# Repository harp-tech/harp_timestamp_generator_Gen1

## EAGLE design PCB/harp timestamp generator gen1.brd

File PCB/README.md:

# Harp Timestamp Generator Gen1

## Licensing

The designs, documentation, and photos available in this repository are free: you can redistribute it and/or modify it under the terms of the used license.
Check file named LICENSE.

Copyright Filipe Carvalho 2021

<br />This work is licensed under a <a rel="license" href="http://creativecommons.org/licenses/by-nc-sa/3.0/igo/">Creative Commons Attribution-NonCommercial-ShareAlike 3.0 IGO License</a>.

If your are interested in obtaining a license to sell this device, please contact filipe@open-ephys.org

[1]: https://docs.google.com/spreadsheets/d/1aobmmEzBDethzIlrm1eg0eYkBqlyX3s9WbA9KgRwVQI/edit?usp=sharing

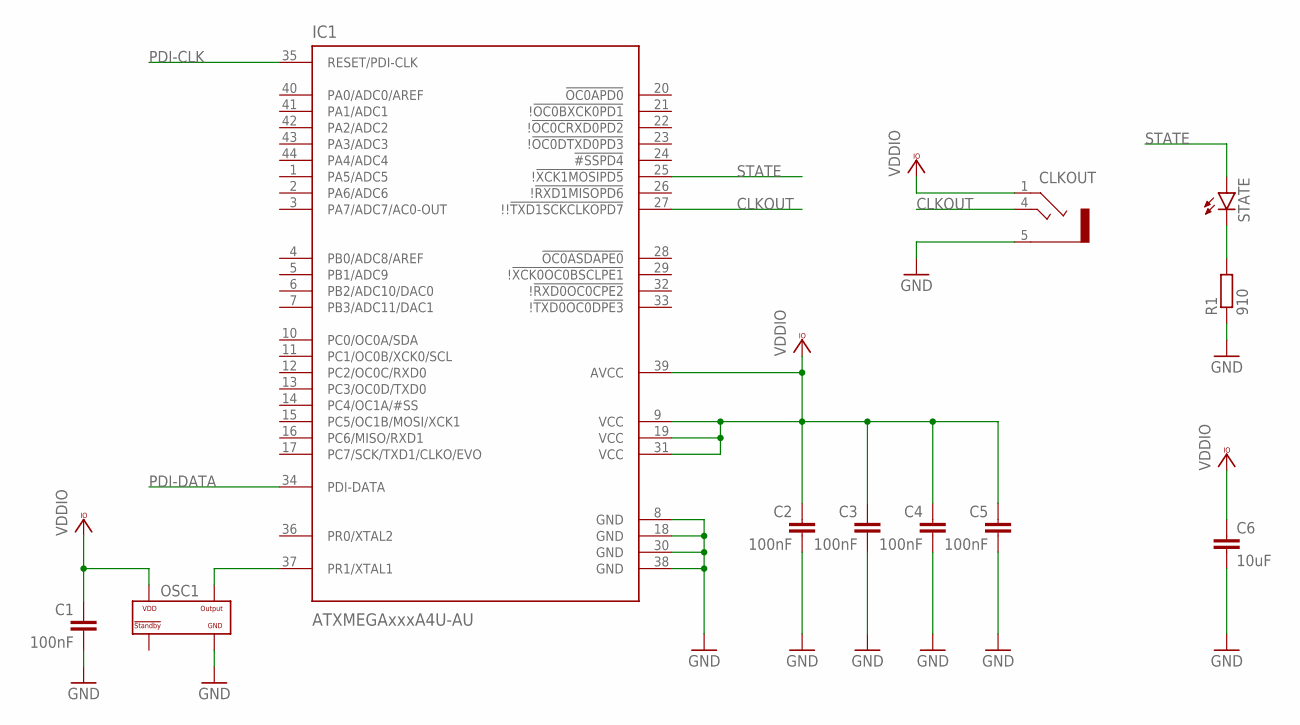
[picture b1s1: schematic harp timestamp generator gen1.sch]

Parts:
C1, C2, C3, C4, C5: 100nF; C0402
C6: 10uF; C0603
CLKOUT: STEREO_JACK; 35RASMT2BHNTRX
IC1: ATXMEGAxxxA4U-AU; QFP80P1200X1200X120-44N
OSC1: CNP-MISCELLANEOUS_OSCILLATOR; CNP-MISCELLANEOUS_OSCILLATOR_3.2X2.5
R1: 910; R0402
STATE: LEDCHIP-LED0603; CHIP-LED0603

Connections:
CLKOUT: CLKOUT.4, IC1.27 (!!!TXD1SCKCLKOPD7)
GND: C1.2, C2.2, C3.2, C4.2, C5.2, C6.2, CLKOUT.5, IC1.8 (GND), IC1.18 (GND), IC1.30 (GND), IC1.38 (GND), OSC1.P$2 (GND), R1.1
unnamed: R1.2, STATE.C
OSC1: IC1.37 (PR1/XTAL1), OSC1.P$3 (OUTPUT)
PDI-CLK: IC1.35 (RESET/PDI-CLK)
PDI-DATA: IC1.34 (PDI-DATA)
STATE: IC1.25 (!!XCK1MOSIPD5), STATE.A
VCCIO: C1.1, C2.1, C3.1, C4.1, C5.1, C6.1, CLKOUT.1, IC1.9 (VCC), IC1.19 (VCC), IC1.31 (VCC), IC1.39 (AVCC), OSC1.P$4 (VDD)

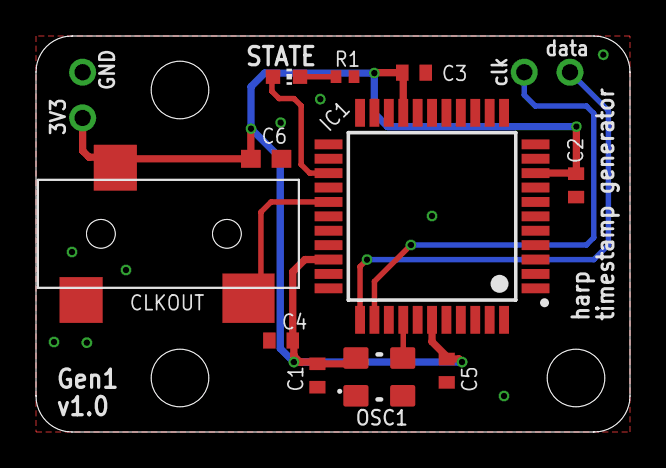
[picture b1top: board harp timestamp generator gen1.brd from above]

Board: 2 copper layers, 33.0 x 22.0 mm, 11 parts (0 on the bottom side), 6 nets.

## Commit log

2021-02-07 Added the first files.
2021-02-07 Corrected Copyright's year.
2021-02-07 Corrected README.md.
2021-02-08 Updated R1 to 910 ohms.
2021-02-08 Added the firmware images.
2021-02-11 Corrected the PN of the audio cable.
2021-02-19 Removed bootloader from Firmware's folder.
2021-02-19 Added fuses state and Atmel-ICE connections.
2021-02-26 Re-designed oscillator footprint for easier manual assembly
